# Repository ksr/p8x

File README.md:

# P8X — Hand-Built 8-Bit TTL CPU

A from-scratch 8-bit CPU built from ~130 74HCT logic chips on an 8-slot DIN41612 backplane. Fully microcoded; the microcode ROM images burned to the EPROMs are the same images the emulator interprets.

The machine now exists **twice**: as the TTL card set, and as an [FPGA
implementation](fpga/) of the same microarchitecture that boots the same
unmodified monitor, OS and toolchain. Both run the microcode from
`microcode/genucode.py`, and the C emulator is the golden reference for both.

The FPGA build also carries a **PGC-class graphics engine** (480x272
RGB565 panel, hardware 3D transforms, command lists, a fabric-parsed
graphics language modeled on the Matrox PG-640A) — see the
[theory of operation](docs/p8x-graphics-theory.md) and the
[graphics programmer's guide](docs/p8x-graphics-guide.md).

New to the abbreviations and signal names? See [GLOSSARY.md](GLOSSARY.md).

**Who made it:** I designed P8X, and it runs on an FPGA. Claude, Anthropic's AI, has been directly involved in its design, coding and documentation. — Ken Rother

## Architecture

- **8-bit data bus, 16-bit address bus**
- **4 × 16-bit pointer registers** (74169 up/down counters): P0 = PC, P1/P2 = general-purpose, P3 = stack pointer (empty-descending). The address bus is *always* driven by one of these — no separate MAR.
- **Registers:** A, B (ALU operands), T/T2 (hidden microcode temporaries), FLAGS (C, Z, N, V)
- **ALU:** 2 × 74181 + 74182 carry-lookahead, with a post-ALU shifter
- **Microcoded control:** 4 × 28C64 EEPROMs; ROM address = IR | step<<8 | cond<<12; **143 opcodes** defined in `microcode/genucode.py` (256 encodings available)
- **Memory map (rev E):** `$0000–$17FF` ROM (6 KB; shrunk from 8 KB 2026-09-14), `$1800–$FEFF` RAM (2× 62256; $1800–$1FFF is a scratch island), `$FF00–$FFFF` I/O (every data address is single-sourced in [`generators/gen_memmap.py`](generators/gen_memmap.py) → `memmap.inc`/`.h`/`.py`; commands pull the scratch/graphics/TPA-base symbols via `//#use mem`)

## Cards

The TTL machine is six core cards plus a PS/2 input card on the backplane, and a
bus test card for bring-up. Every board is designed and routed in **KiCad** (4-layer;
the plug-in cards are 280 × 140 mm) with orderable Gerbers in `hardware/<board>/kicad/`;
none has been fabricated yet. See [hardware/KICAD-BOARDS.md](hardware/KICAD-BOARDS.md)
and [hardware/RECONCILIATION.md](hardware/RECONCILIATION.md) (build readiness).

| Card | Function |
|------|----------|
| Control / Microcode | Clock, reset, sequencer, microcode EPROMs, IR, condition mux, front-panel |
| Register Bank | P0–P3 16-bit pointer registers, address bus drivers |
| ALU | A, B, T, T2 registers; 74181 ALU; shifter; FLAGS |
| Memory | 28C256 EEPROM (6 KB ROM window) + 2× 62256 SRAM, address decode (rev F) |
| I/O | Switches, LEDs, bus monitor, two 6850 ACIAs (RS-232, two DB9s) |
| CF-IDE | Two CompactFlash drives in 8-bit True IDE mode, at $FF10–$FF17 and $FF18–$FF1F |
| PS/2 | Keyboard + mouse ports at $FF58–$FF5F; an ATmega1284P behind a latch bridge |
| Bus test | Bring-up tool: a Raspberry Pi Pico drives the bus one microcycle at a time over USB |

The cards plug into a passive 8-slot backplane over a 96-pin DIN 41612 bus (rev C2).
The Eagle CAD of the first board generation is frozen (rev E) in each board's
`eagle-deprecated/` directory.

## Toolchain

| Tool | Location | Purpose |
|------|----------|---------|
| `microcode/genucode.py` | `microcode/` | Microcode generator → `u0–u3.bin` EPROM images |
| `assembler/p8xasm.py` | `assembler/` | Two-pass assembler, shares opcode table with genucode.py |
| `emulator/p8xemu.c` | `emulator/` | Cycle-accurate emulator, interprets the same u0–u3.bin images |
| `firmware/p8xmon.asm` | `firmware/` | ROM monitor (E/D/I/F/B/G/? commands) + BIOS jump table at `$0100` |
| `os/p8xos.asm` | `os/` | P8X/OS, RAM-resident disk OS booted from CF ([guide](os/README.md)) |
| `tools/p8xfs.py` | `tools/` | Host-side P8XFS disk-image tool (create/boot/put/get/ls) |
| `basic/p8xbasic.asm` | `basic/` | BASIC interpreter — disk-bootable or run-from-OS builds ([guide](basic/README.md)) |
| `apps/p8xedit.asm`, `apps/p8xasm.asm`, `apps/p8xcc.asm` | `apps/` | On-target toolchain: line editor + native two-pass assembler + native C compiler (`cc`), as `/bin` programs ([guide](apps/README.md)) |
| `compiler/p8cc.py` | `compiler/` | C cross-compiler (subset) → P8X asm → RUNnable `.bin` ([guide](compiler/README.md)) |
| `generators/gen_p8xopc.py` | `generators/` | Opcode table for the native assembler, generated from `genucode.OPC` |
| `generators/gen_eagle.py` | `generators/` | The canonical board netlists (`CARDS`, `busnet()`); its Eagle output is frozen at rev E |
| `generators/gen_kicad.py`, `build.sh` | `generators/` | KiCad boards from those netlists: placement, Freerouting, Gerbers, and the ERC/DRC readiness check |

**Generators are canon.** Never hand-edit board files (`.kicad_pcb`, and the frozen Eagle `.sch`/`.brd`) or ROM binaries — they are build artifacts. Edit the generator and regenerate. See [generators/README.md](generators/README.md) for what each script does and how to run it.

## Quick Start

Setting up a new machine? See [SETUP.md](SETUP.md) for the full toolchain, tier by
tier, and run `python3 tools/setup_check.py` to see what is installed and what each
work area still needs. Only the core-software tier is required to build and test.

```sh
# Build the emulator and regenerate microcode images
cd emulator && make

# Run the smoke tests (message print, JSR/RTS round-trip, branch countdown)
make test

# Rebuild a KiCad board: placement -> Freerouting -> Gerbers + renders -> the
# ERC/gate-sim/DRC/keepout/fab readiness check (needs KiCad 10 and a Freerouting
# jar; `all` builds every board). The netlists come from generators/gen_eagle.py.
cd ..
sh generators/build.sh memory-card
sh generators/check_card.sh memory-card          # the readiness check alone

# Reference PDFs (run from anywhere):
cd hardware
python3 ../generators/gen_bus_pdf.py              # bus definition PDF (hardware/backplane/)
python3 ../microcode/gen_progguide.py             # programmer's guide (-> docs/)
```

### EEPROM / programmer images

Both build paths emit **Intel HEX** alongside the raw `.bin`, for loading into an
EEPROM programmer:

- **Microcode** — `microcode/genucode.py` writes `u0–u3.bin` (what the emulator
  and tests load); the matching Intel HEX for the four 28C64 control-store EPROMs
  is produced into `rom/` by `make rom` (see below).
- **Program ROM** — the assembled monitor + BIOS for the 28C256 at `$0000`
  (about 4.9 KB of the 6 KB window; BASIC is no longer ROM-resident). `make rom` builds it into `rom/`.
- **Any other binary** — `python3 tools/bin2hex.py in.bin out.hex [base]`
  (e.g. a monitor built directly with `p8xasm.py`).

For a ready-to-burn set at fixed paths, run `cd emulator && make rom` (or
`sh tools/build_rom.sh`). It refreshes the four control-store EPROMs in
`microcode/` and writes the program ROM to `rom/p8x-prog-rom.{bin,hex}`. Both
are committed; see [rom/README.md](rom/README.md) for the chip map.

## Documentation

The documents below are also built into the project website, [p8x.cottageworker.com](https://p8x.cottageworker.com) (`website/`, MkDocs; published on every push to `main`).

| Document | Description |
|----------|-------------|
| [hardware/backplane/p8x-bus-definition.md](hardware/backplane/p8x-bus-definition.md) | Authoritative 96-pin bus pinout, signal descriptions, DOE/DLD encoding, microcode word layout |
| [hardware/backplane/p8x-backplane-design.md](hardware/backplane/p8x-backplane-design.md) | PCB stackup, termination analysis, BOM |
| [docs/p8x-card-standards.md](docs/p8x-card-standards.md) | Design rules that apply to every plug-in card |
| [docs/p8x-system-design.md](docs/p8x-system-design.md) | System and card-by-card architecture reference |
| [hardware/cf-card/p8x-cf-os-design.md](hardware/cf-card/p8x-cf-os-design.md) | CF-IDE hardware + P8X/OS design |
| [hardware/cf-card/p8xfs-v2-hierarchical.md](hardware/cf-card/p8xfs-v2-hierarchical.md) | P8XFS v2 hierarchical filesystem spec |
| [docs/p8x-programmers-guide.pdf](docs/p8x-programmers-guide.pdf) | Generated instruction set reference |
| [basic/p8x-basic-guide.md](basic/p8x-basic-guide.md) | P8X BASIC language reference (statements, expressions, graphics, examples) |
| [fpga/README.md](fpga/README.md) | FPGA build: milestones, getting started, both paths |
| [fpga/docs/architecture.md](fpga/docs/architecture.md) | FPGA module hierarchy, peripheral map, graphics, co-sim spec |
| [fpga/rtl/README.md](fpga/rtl/README.md) | What is shared vs sim-only, and the `cen` / `sc_en` contracts |
| [fpga/sim/README.md](fpga/sim/README.md) | How the co-sim trace-diff works, and the graphics frame diff |
| [BACKLOG.md](BACKLOG.md) | Live work only: NEXT / IDEAS / VERIFY / WONT-DO |
| [BACKLOG-DONE.md](BACKLOG-DONE.md) | Completed work + the project log |

### Per-card guides

Each board has its own directory under `hardware/` holding everything about it —
the KiCad board and its Gerbers, placement PDF and renders (`kicad/`), a README
explaining how the circuit works chip by chip, any board-specific design docs, and
the frozen Eagle files (`eagle-deprecated/`):

| Card | Directory |
|------|-----------|
| Control / Microcode | [hardware/control-card/](hardware/control-card/README.md) |
| Register Bank | [hardware/regbank-card/](hardware/regbank-card/README.md) |
| ALU | [hardware/alu-card/](hardware/alu-card/README.md) |
| Memory | [hardware/memory-card/](hardware/memory-card/README.md) |
| I/O | [hardware/io-card/](hardware/io-card/README.md) |
| CF-IDE | [hardware/cf-card/](hardware/cf-card/README.md) |
| PS/2 | [hardware/ps2-card/](hardware/ps2-card/README.md) |
| Bus test | [hardware/bustest-card/](hardware/bustest-card/p8x-bustest-card-design.md) |
| Backplane | [hardware/backplane/](hardware/backplane/p8x-backplane-design.md) |

## FPGA implementation

A standalone [FPGA build](fpga/) on a **Sipeed Tang Nano 20K** (Gowin GW2AR-18)
runs the whole machine — CPU, memory, ACIA console, microSD disk, and a 4.3"
480x272 graphics panel — from one chip and a USB cable. It is a **parallel track to the TTL build, not a replacement**:
same horizontal microcode word, same sequencer, same pointer/address model, so
the monitor, OS, BASIC, C compiler and assembler run **unmodified**.

| Milestone | State |
|-----------|-------|
| 0 First light (UART echo + heartbeat) | done |
| 1 CPU core in simulation, all 88 opcodes of the time | done |
| 2 ACIA + driven console in simulation | done |
| 3 Core on real hardware, full 64K map | done |
| 4 microSD disk — P8X/OS boots from card | done |
| 5 Clock-up + IRQ | next |
| 6 Graphics: 480x272 panel + drawing engine | done |

As built: **9 MHz** effective (27 MHz fabric, three phases per microcycle). The
CPU-only build is 40/46 block RAMs at ~48 MHz Fmax; adding the graphics panel takes
it to 44/46 and 13288/20736 LUT4, with Fmax measured at 38.8 MHz — still four times
the clock it runs at. P8X is programmed into the board's flash, so it comes up
standalone on power.

**Graphics** (`build.sh lcd`) adds the panel's native 480×272 framebuffer in
**RGB565 direct colour** — a pixel IS its colour, 65,536 of them — living in
the Tang Nano's in-package SDRAM behind a streaming controller, with a drawing
engine driven by BASIC in one window-space coordinate system (y up, the
PGC's own): `COLOR r,g,b` (or one packed value), `CLS`, `PIXELW`, `LINE`,
`BOX`, `CIRCLE` (a second radius gives an ellipse), `IMAGE` (draws a
P8I picture file — `tools/p8img.py` converts anything into one), the
`PIXELR(x,y)` and `RGB(r,g,b)` functions — plus the full PGC graphics
language as native statements (`MOVE`/`DRAW`/`POLY`/`RECT`, matrices, 3D,
command lists; see `man basic`). Text is the PGC's own stroke `TEXT`,
drawn card-side from the font the OS streams from `/FONT.GL` at boot
(GTEXT and its software rasterizer retired 2026-09-01). The drawing
statements emit that language; the engine lives in the device, so a
filled box costs the same handful of instructions as an empty one.
There is one geometry and no modes or palette to manage.
The same device is modelled in `p8xemu`, and the two are byte-compared frame
by frame.

**3D** (stages 7–10, `fpga/tang-nano-20k/sdram/STAGE*.md`): a wireframe
pipeline available from C in software (`//#use gfx` + `//#use g3d`),
accelerated by the **MDU** (a memory-mapped hardware multiply-divide unit at
`$FF30`), or fully on the card through the **GL engine** (`$FF50`): card-side
modeling and viewing matrices, clipping and projection, command lists stored in
SDRAM, and page-flipped double buffering. (The stage-8 geometry engine's
`$FF40` register window was retired at stage 10b; the GL engine is its
successor.) The same program picks the fastest fitted path at runtime; `cube`
on the shipped disk is a self-spinning GL command list, with the software path
as its fallback (`man cube`, `man g3d`).

**Verification is the point.** Every milestone is "make the RTL match the
emulator": the same program runs on both and their per-cycle architectural state
is diffed, so a divergence is a bug with an exact microcycle and signal rather
than a mystery. `fpga/sim/isa_test.asm` drives the original 88 opcodes through that diff;
the 55 added since are microcode only (no new hardware), and the RTL runs them from
the same images.

```sh
fpga/sim/run.sh 60000 isa_test.asm          # co-sim, the original 88 opcodes
fpga/sim/console.sh "" os/run-disk.img      # interactive console on the RTL
fpga/tang-nano-20k/build.sh cpu load        # build + program the board
```

## Status

- Emulator working: 143 opcodes, ACIA on stdin/stdout, CF-IDE disk model (`-c `), interactive I/O card (switches `-s`, LED trace `-L`), verified against microcode images
- Assembler working: two-pass, full expression support, shares opcode table with microcode generator
- KiCad boards designed and routed for the six CPU cards, the PS/2 card, the bus test card and the backplane (9 boards, 0 unconnected, Gerbers in each `kicad/`); none fabricated yet. The Eagle files of the first generation are frozen in `eagle-deprecated/`. (The standalone LED test card was a CAD-workflow trial, never built — deprecated and moved to `hardware/deprecated/led-card/`; its I/O address `$FF0C` is now free.)
- ROM monitor boots in the emulator; its filesystem hooks (`I`/`F`/`B`) run end to end against a CF image (`make test-cf`)
- P8X/OS v1.0 — full shell over flat **and hierarchical (P8XFS v2)** volumes. Built-in commands: `cd`/`mkdir`/`rmdir`/`load`/`run`/`save`/`del`/`path`/`pack`/`fsck`/`format`/`mount`/`umount`/`help`/`exit`/`man`/`sh`/`make`/`bootload` (`make` builds a target from a CWD `Makefile`; `bootload file` installs a freshly-built OS image into the boot sectors so the next `exit`+`B` runs it — the on-target OS-update step, closing the self-hosting loop) (the minimal-kernel split moved the pure-viewer/memory commands to `/bin`, including `dump`/`dep` — only `pack`/`fsck` remain resident because they mutate/scan the filesystem). **Dual CompactFlash** — a second card is **mounted at `/d1`** in one unified namespace (drive 0 is the root), so ordinary paths reach it with drive-unaware commands: `cd /d1`, `cat /d1/NOTES`, `grep x /d1/SRC/*.C`, cross-mount `cp /d1/A /B`. A single mount redirect in `FRESOLVE`/`RV_START` does the routing; **`cp -r /d1/dir /dir`** recursively copies a subtree across the mount (card provisioning), creating directories via the `SYS_MKDIR` syscall. **Userland commands in `/bin`** (written in C, run by bare name via implicit RUN + a `/bin` search PATH, or explicit `run`): **`dir`/`pwd`/`tree`/`cat`/`wc`/`grep`/`cp`/`mv`/`head`/`tail`/`more`/`sort`/`uniq`/`sed`/`awk`/`find`/`diff`/`cmp`/`vi`/`touch`/`man`/`dump`/`dep`/`examine`/`disasm`** (`dir README.TXT` lists a file / `dir R*` a glob, `dir -R`, `cp -r`, a VT100 `vi` screen editor, `man <cmd>` reading `/man`, `awk '{print $2}'` field processing, `examine` = interactive memory examine/modify like the monitor's `E`, etc.) — see [os/commands/](os/commands/README.md). Path resolution + CWD-path prompt; I/O redirection (`<`/`>`) and two-stage pipes (`a | b`); line editing (backspace/DEL, Ctrl-D EOF, **up/down-arrow command history** — an 8-line RAM ring — and **Tab autocomplete** of commands/paths with common-prefix fill + a match list on the second Tab); **`pack`** compacts the directory tree and **`fsck`** checks integrity on-target; host-side `p8xfs.py` builds (`--v2`), navigates, and `fsck`s images (`make test-os`)
- BASIC builds two ways from one source: disk-bootable (`B`) and a run-from-OS TPA program (`run BASIC.bin`) — `make test-basic` (ROM-resident BASIC was removed to reclaim ROM space; the old standalone `$0000` build was retired in 2026-08 when BASIC's console I/O moved onto the BIOS, which needs the monitor resident)
- On-target toolchain: **EDIT** (line editor) + **ASM** (native two-pass assembler) + **CC** (a from-scratch C compiler written in asm) as `/bin` programs — edit → **compile (`cc x.c >x.asm`)** → assemble → run a program entirely on the machine; ASM output is byte-identical to the host assembler across the whole opcode table (`make test-os`, see [apps/](apps/README.md)). **Rebuild any command on-target** — every command's source rides along under `/src/commands/{c,asm}` (plus shared `lib_*` helpers), each dir carrying a real **`Makefile`** (`target: deps` + TAB recipe, with `all`/`clean`/`install` targets). The **`make`** built-in reads the CWD `Makefile`, resolves prerequisites depth-first (shared deps built once), and drives `cc`→`asm` (or `asm` alone): `cd /src/commands/c && make pwd` rebuilds one command, `make all` the whole dir into `bin/`, `make install` publishes them over `/bin`, `make clean` removes the build outputs — see [os/commands/](os/commands/README.md). (P8X shell scripts end in `.sh`; `make` uses proper Makefiles.)
- **Native C compiler — Milestone B achieved.** `apps/p8xcc.asm` (`/bin/cc`) is a from-scratch, single-pass C compiler written directly in assembly, small enough to compile C **entirely on the machine** (front *and* back end) where the optimizing `p8cc.c` codegen — ~82 KB, larger than the whole 64 KB address space — never could. Through v0.28 it covers: functions, direct **and mutual** recursion, pointers + pass-by-reference, `int`/`char` arrays with `[]` and decay, **structs** (`.`/`->`), globals, the full operator set (`+ - * / % << >> & ^ | && || ?:`, `++`/`--`/`+=`/`-=`, comparisons, unary `- ! * &`), hex/char/string literals with escapes, `//`+`/* */` comments, a recursive **`//#use`** preprocessor (splices `/lib/lib_*.c`) plus object-like **`//#define`** macros (e.g. `//#use abi` names the BIOS/OS addresses so a command writes `bios(FOPEN, RDBUF, 0)`), and the `putchar`/`puts`/`getchar`/`peek`/`poke`/`argstr`/`bios` builtins. It compiles real OS command source: **`pwd.c` → `cc` → `asm` → runs** correctly on-target. Known gaps are listed under "cc — KNOWN LIMITATIONS" in `BACKLOG-DONE.md` (with the Milestone A/B record).
- **Host C compiler** — `compiler/p8cc.py` (the primary build tool: every `/bin` command is compiled with it) plus `compiler/p8cc.c`, the same compiler rewritten in its own subset that **self-compiles** ("small C in small C", Milestone A). Full subset incl. `struct`/`union`, global initializers, and the operators above (`make test-c`, host-vs-self differential `c_selfhost_test`, see [compiler/](compiler/README.md)).
- BIOS **file API**: byte streams (`FOPEN`/`FGETB`, `FWOPEN`/`FPUTB`/`FCLOSE`), path resolution into subdirectories (`FRESOLVE`), name formatting (`FNORM`), and directory iteration (`FOPENDIR`/`FNEXT`) — the assembler rides on the streams and self-hosts (`make test-cf`)
- **FPGA (Tang Nano 20K):** the same microarchitecture in Verilog, verified against the emulator cycle-for-cycle across the original 88 opcodes, then run on real hardware — monitor over USB serial, full 64K map, and **P8X/OS booting from a microSD** with the whole `/bin` toolchain. The board wrote its own disk: `fpga/tang-nano-20k/tools/imgload.asm` streams a P8XFS image over the console and writes it with `CFWRITE`, so no host root or card reader is needed. See [fpga/](fpga/README.md)
- **Next:** multi-stage pipes (`a | b | c`); open-by-name as one syscall (`SYS_OPEN`); the IRQ-controller hardware card; hardware bring-up (DIN 41612 footprint check against the physical connectors, order the backplane first); FPGA milestone 5 (clock-up + IRQ). Current state in [docs/p8x-status.md](docs/p8x-status.md), the working list in [BACKLOG.md](BACKLOG.md)

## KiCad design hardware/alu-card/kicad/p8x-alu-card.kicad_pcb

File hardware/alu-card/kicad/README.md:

# alu-card -- KiCad

Generated by `generators/gen_kicad.py` from the canonical gen_eagle netlist
(`CARDS["alu-card"]`), same standard as the memory card: 4-layer (F/B signals,
In1=GND, In2=VCC planes), a bypass cap above each IC, a labelled LED/jumper bank,
part values on silk. Routed with Freerouting. GENERATORS ARE CANON -- edit
`gen_kicad.py` and re-run `generators/build_kicad_card.sh alu-card`.

| File | What |
|------|------|
| `p8x-alu-card.kicad_pcb` | the board |
| `p8x-alu-card.ses` | the Freerouting routing |
| `p8x-alu-card-gerbers.zip` | orderable gerbers |
| `p8x-alu-card-placement.pdf` | parts placement (refs+values) |
| `p8x-alu-card-render-top.png` / `-3d.png` | renders |

Exotic parts use the closest standard KiCad footprint (flagged when built).

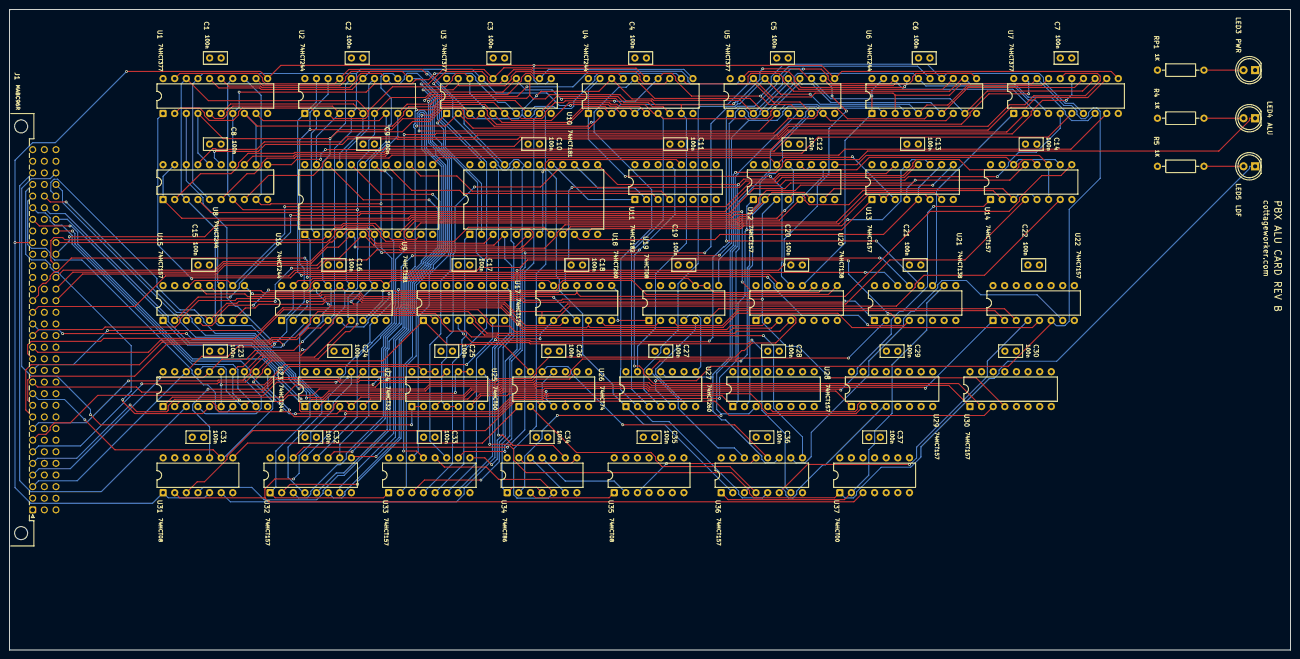
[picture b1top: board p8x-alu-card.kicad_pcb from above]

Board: 4 copper layers, 280.0 x 140.0 mm, 81 parts (0 on the bottom side), 158 nets.

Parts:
C1, C2, C3, C4, C5, C6, C7, C8, C9, C10, C11, C12, C13, C14, C15, C16, C17, C18, C19, C20, C21, C22, C23, C24, C25, C26, C27, C28, C29, C30, C31, C32, C33, C34, C35, C36, C37: 100nF; C_Disc_D5.0mm_W2.5mm_P2.50mm
J1: MABC96R; DIN41612_C_3x32_Male_Horizontal_THT
LED3, LED4: GRN; LED_D5.0mm
LED5: YEL; LED_D5.0mm
R4, R5: 1K; R_Axial_DIN0207_L6.3mm_D2.5mm_P10.16mm_Horizontal
RP1: 1K; R_Axial_DIN0207_L6.3mm_D2.5mm_P10.16mm_Horizontal
U1, U3, U5, U7: 74HCT377; DIP-20_W7.62mm
U2, U4, U6, U8, U16, U23: 74HCT244; DIP-20_W7.62mm
U9, U10: 74HCT181; DIP-24_W15.24mm
U11: 74HCT182; DIP-16_W7.62mm
U12, U13, U14, U15, U22, U28, U29, U30, U32, U33, U36: 74HCT157; DIP-16_W7.62mm
U17: 74HCT175; DIP-16_W7.62mm
U18, U27: 74HCT260; DIP-14_W7.62mm
U19, U31, U35: 74HCT08; DIP-14_W7.62mm
U20, U21: 74HCT138; DIP-16_W7.62mm
U24: 74HCT32; DIP-14_W7.62mm
U25, U37: 74HCT00; DIP-14_W7.62mm
U26: 74HCT74; DIP-14_W7.62mm
U34: 74HCT86; DIP-14_W7.62mm

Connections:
-CCLR: U26.1, U31.8
-CLRCb: U25.11, U31.10
-DOEA: U2.1, U2.19, U20.14
-DOEALU: U16.1, U16.19, U19.9, U19.10, U20.10
-DOEB: U4.1, U4.19, U20.13
-DOEFLG: U20.9, U23.1
-DOET: U6.1, U6.19, U20.12
-DOET2: U8.1, U8.19, U20.11
-LDA: U1.1, U21.14
-LDB: U3.1, U21.13
-LDFL: U21.10, U36.1, U37.2
-LDT: U5.1, U21.12
-LDT2: U7.1, U21.11
-RES: J1.a11, U17.1, U26.13, U31.9
-SETCb: U25.3, U26.4
ALUK: LED4.1, U19.8
ALUM: J1.c23, U9.8, U10.8
ALUS0: J1.c19, U9.6, U10.6
ALUS1: J1.c20, U9.5, U10.5
ALUS2: J1.c21, U9.4, U10.4, U34.9
ALUS3: J1.c22, U9.3, U10.3
AQ0: U1.2, U2.2, U9.2
AQ1: U1.5, U2.4, U9.23
AQ2: U1.6, U2.6, U9.21
AQ3: U1.9, U2.8, U9.19
AQ4: U1.12, U2.11, U10.2
AQ5: U1.15, U2.13, U10.23
AQ6: U1.16, U2.15, U10.21
AQ7: U1.19, U2.17, U10.19, U34.1, U34.4
BMX0: U9.1, U32.4
BMX1: U9.22, U32.7
BMX2: U9.20, U32.9
BMX3: U9.18, U32.12
BMX4: U10.1, U33.4
BMX5: U10.22, U33.7
BMX6: U10.20, U33.9
BMX7: U10.18, U33.12, U34.5
BQ0: U3.2, U4.2, U32.2
BQ1: U3.5, U4.4, U32.5
BQ2: U3.6, U4.6, U32.11
BQ3: U3.9, U4.8, U32.14
BQ4: U3.12, U4.11, U33.2
BQ5: U3.15, U4.13, U33.5
BQ6: U3.16, U4.15, U33.11
BQ7: U3.19, U4.17, U33.14
BSEL: J1.b28, U32.1, U33.1
CFLG: U10.16, U25.4, U25.5
CFLGI: U25.6, U29.2
CG0: U9.17, U11.3
CG1: U10.17, U11.1
CIN: J1.c24, U9.7, U11.13, U30.2
CLK: J1.a24, U1.11, U3.11, U5.11, U7.11, U31.1, U31.5
CLKFC: U26.3, U26.11, U31.3
CLKFZN: U17.9, U31.6
CLRC: J1.b27, U25.12, U25.13
CNX: U10.7, U11.12
CP0: U9.15, U11.4
CP1: U10.15, U11.2
D0: J1.a3, U1.3, U2.18, U3.3, U4.18, U5.3, U6.18, U7.3, U8.18, U16.18, U23.18, U27.1, U36.2
D1: J1.a4, U1.4, U2.16, U3.4, U4.16, U5.4, U6.16, U7.4, U8.16, U16.16, U23.16, U27.2, U36.5
D2: J1.a5, U1.7, U2.14, U3.7, U4.14, U5.7, U6.14, U7.7, U8.14, U16.14, U23.14, U27.11, U36.11
D3: J1.a6, U1.8, U2.12, U3.8, U4.12, U5.8, U6.12, U7.8, U8.12, U16.12, U23.12, U27.12, U36.14
D4: J1.a7, U1.13, U2.9, U3.13, U4.9, U5.13, U6.9, U7.13, U8.9, U16.9, U27.13
D5: J1.a8, U1.14, U2.7, U3.14, U4.7, U5.14, U6.7, U7.14, U8.7, U16.7, U27.3
D6: J1.a9, U1.17, U2.5, U3.17, U4.5, U5.17, U6.5, U7.17, U8.5, U16.5, U27.4
D7: J1.a10, U1.18, U2.3, U3.18, U4.3, U5.18, U6.3, U7.18, U8.3, U16.3, U22.6, U27.5
DLD0: J1.a16, U21.1
DLD1: J1.a17, U21.2
DLD2: J1.a18, U21.3
DLD3: J1.a19, U21.4
DOE0: J1.a12, U20.1
DOE1: J1.a13, U20.2
DOE2: J1.a14, U20.3
DOE3: J1.a15, U20.4
F0: U9.9, U12.2, U12.6, U28.2
F1: U9.10, U12.5, U12.10
F2: U9.11, U12.11, U12.13
F3: U9.13, U12.14, U13.3
F4: U10.9, U13.2, U13.6
F5: U10.10, U13.5, U13.10
F6: U10.11, U13.11, U13.13
F7: U10.13, U13.14, U28.3, U34.2
FC: J1.a27, U23.9
FENALL: U24.8, U31.4
FENC: U24.10, U31.2, U37.3
FENZN: U24.3, U24.9
FN: J1.a29, U23.5
FQC: U23.2, U23.11, U26.5, U30.3
FQN: U17.7, U23.6, U23.15
FQV: U23.8, U23.17, U26.9
FQZ: U17.2, U23.4, U23.13
FV: J1.a30, U23.3
FZ: J1.a28, U23.7
G0: U12.4, U14.2
G1: U12.7, U14.3, U14.5
G2: U12.9, U14.6, U14.11
G3: U12.12, U14.10, U14.14
G4: U13.4, U14.13, U15.2
G5: U13.7, U15.3, U15.5
G6: U13.9, U15.6, U15.11
G7: U13.12, U15.10, U15.14
GND: C1.2, C2.2, C3.2, C4.2, C5.2, C6.2, C7.2, C8.2, C9.2, C10.2, C11.2, C12.2, C13.2, C14.2, C15.2, C16.2, C17.2, C18.2, C19.2, C20.2, C21.2, C22.2, C23.2, C24.2, C25.2, C26.2, C27.2, C28.2, C29.2, C30.2, C31.2, C32.2, C33.2, C34.2, C35.2, C36.2, C37.2, J1.a31, J1.a32, J1.b3, J1.b5, J1.b7, J1.b9, J1.b11, J1.b13, J1.b15, J1.b17, J1.b19, J1.b21, J1.b23, J1.b25, J1.b31, J1.b32, J1.c31, J1.c32, LED3.1, U1.10, U2.10, U3.10, U4.10, U5.10, U6.10, U7.10, U8.10, U9.12, U10.12, U11.8, U12.8, U12.15, U13.8, U13.15, U14.8, U14.15, U15.8, U15.15, U16.10, U17.8, U17.12, U17.13, U18.7, U18.9, U18.10, U19.7, U19.12, U19.13, U20.5, U20.8, U21.5, U21.8, U22.8, U22.10, U22.11, U22.13, U22.14, U22.15, U23.10, U23.19, U24.7, U24.12, U24.13, U25.7, U26.7, U27.7, U27.9, U27.10, U28.5, U28.6, U28.8, U28.10, U28.11, U28.13, U28.14, U28.15, U29.5, U29.6, U29.8, U29.10, U29.11, U29.13, U29.14, U29.15, U30.5, U30.6, U30.8, U30.10, U30.11, U30.13, U30.14, U30.15, U31.7, U31.12, U31.13, U32.8, U32.15, U33.8, U33.15, U34.7, U35.4, U35.5, U35.7, U35.9, U35.10, U35.12, U35.13, U36.8, U36.15, U37.4, U37.5, U37.7, U37.9, U37.10, U37.12, U37.13
LDF: J1.a26, U24.1, U25.9, U25.10
LDFK: LED5.1, U25.8, U37.1
LDZN: J1.c28, U22.1, U24.2
LEDAL: LED4.2, R4.2
LEDLF: LED5.2, R5.2
LEDP: LED3.2, RP1.2
NC: U29.4, U36.3
NS2: U34.8, U34.13
NSRC: U22.7, U36.10
R0: U14.4, U16.2, U18.1
R1: U14.7, U16.4, U18.2
R2: U14.9, U16.6, U18.11
R3: U14.12, U16.8, U18.12
R4: U15.4, U16.11, U18.13
R5: U15.7, U16.13, U18.3
R6: U15.9, U16.15, U18.4
R7: U15.12, U16.17, U18.5, U22.5
RC: U26.2, U36.4
RN: U17.5, U36.9
RV: U26.12, U36.12
RZ: U17.4, U36.7
SETC: J1.c30, U25.1, U25.2
SH0: J1.c25, U12.1, U13.1, U24.4, U28.1
SH1: J1.c26, U14.1, U15.1, U24.5
SHANY: U24.6, U29.1
SHCIN: J1.c29, U30.1
SHIN: U12.3, U15.13, U30.4
SHOUT: U28.4, U29.3
T2Q0: U7.2, U8.2
T2Q1: U7.5, U8.4
T2Q2: U7.6, U8.6
T2Q3: U7.9, U8.8
T2Q4: U7.12, U8.11
T2Q5: U7.15, U8.13
T2Q6: U7.16, U8.15
T2Q7: U7.19, U8.17
TQ0: U5.2, U6.2, U32.3
TQ1: U5.5, U6.4, U32.6
TQ2: U5.6, U6.6, U32.10
TQ3: U5.9, U6.8, U32.13
TQ4: U5.12, U6.11, U33.3
TQ5: U5.15, U6.13, U33.6
TQ6: U5.16, U6.15, U33.10
TQ7: U5.19, U6.17, U33.13
VCC: C1.1, C2.1, C3.1, C4.1, C5.1, C6.1, C7.1, C8.1, C9.1, C10.1, C11.1, C12.1, C13.1, C14.1, C15.1, C16.1, C17.1, C18.1, C19.1, C20.1, C21.1, C22.1, C23.1, C24.1, C25.1, C26.1, C27.1, C28.1, C29.1, C30.1, C31.1, C32.1, C33.1, C34.1, C35.1, C36.1, C37.1, J1.a1, J1.a2, J1.b1, J1.b2, J1.c1, J1.c2, R4.1, R5.1, RP1.1, U1.20, U2.20, U3.20, U4.20, U5.20, U6.20, U7.20, U8.20, U9.24, U10.24, U11.5, U11.6, U11.14, U11.15, U11.16, U12.16, U13.16, U14.16, U15.16, U16.20, U17.16, U18.14, U19.14, U20.6, U20.16, U21.6, U21.16, U22.16, U23.20, U24.14, U25.14, U26.10, U26.14, U27.14, U28.16, U29.16, U30.16, U31.14, U32.16, U33.16, U34.10, U34.14, U35.14, U36.16, U37.14
VSRC: U35.3, U36.13
VX1: U34.3, U35.1
VX2: U34.6, U34.12
VX4: U34.11, U35.2
ZBH: U19.5, U27.6
ZBL: U19.4, U27.8
ZBUS: U19.6, U22.3
ZFLG: U19.3, U22.2
ZH: U18.6, U19.2
ZL: U18.8, U19.1
ZSRC: U22.4, U36.6

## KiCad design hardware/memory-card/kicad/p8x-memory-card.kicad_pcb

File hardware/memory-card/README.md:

# Memory Card

> **Theory of operation:** [p8x-memory-card-theory.md](p8x-memory-card-theory.md) — deep walkthrough of inputs/outputs, signal flow, and logic.

Provides the system's ROM and RAM and gates them onto the data bus. It decodes the
address bus to pick ROM vs RAM, keeps both off the data bus during I/O accesses,
and generates a clean write strobe.

> **Build the KiCad rev F board.** The 2026-09-14 ROM shrink made the map
> **6 KB ROM `$0000–$17FF`** with **`$1800–$1FFF` a RAM scratch island** (written
> by the OS/BIOS, so it must be RAM). The KiCad board in [`kicad/`](kicad/README.md)
> (rev F, routed, not yet fabricated) implements that decode on three spare gates,
> with no new chips: ROM `!CE` gains an `A11·A12` term and low-RAM U10 widens to
> `$1800–$7FFF`. The chip-by-chip text below describes the **rev E** netlist in
> `gen_eagle.py` (8 KB ROM, `$0000–$1FFF`), which `kicad/mem_revf.py` rewires to
> rev F for both the KiCad board and its schematic; the frozen Eagle `.sch` in `eagle-deprecated/` is rev E too and
> must not be built.

| Region | Device | Size |
|--------|--------|------|
| `$0000–$17FF` | 28C64 ROM (U1) | 6 KB — monitor + BIOS (BASIC is a disk program) |
| `$1800–$1FFF` | 62256 SRAM (U10) | 2 KB scratch island (IBUF/SBUF/BIOS scratch) |
| `$2000–$7FFF` | 62256 SRAM (U10) | 24 KB |
| `$8000–$FEFF` | 62256 SRAM (U2) | 32 KB (minus the I/O page) |
| `$FF00–$FFFF` | — (I/O page) | RAM inhibited; handled by I/O & CF cards |

(Rev E after the 2026-09-14 shrink: 6 KB ROM at `$0000–$17FF`; two 62256 cover
`$1800–$FEFF` = 58 KB; OS loads at `$2000`.)

> This README describes the circuit as actually built in
> [`generators/gen_eagle.py`](../../generators/gen_eagle.py). See
> [p8x-system-design.md §6](../../docs/p8x-system-design.md) for the overview and
> [p8x-bus-definition.md](../backplane/p8x-bus-definition.md) for bus pins.

## Chip inventory

| Ref | Device | Role |
|-----|--------|------|
| U1 | 28C256 (low 8 KB used; or a 28C64) | ROM (rev E: 8 KB, $0000–$1FFF; rev F: 6 KB, $0000–$17FF) |
| U2 | 62256 | SRAM, 32 KB (`$8000–$FEFF`) |
| U10 | 62256 | SRAM, 24 KB (`$2000–$7FFF`, rev E; `$1800–$7FFF` in rev F) |
| U3 | 74245 | Bidirectional data-bus transceiver |
| U4 | 7430 | 8-input NAND — I/O page ($FFxx) detector |
| U5 | 74138 | DOE decoder (read enable) |
| U6 | 74138 | DLD decoder (write strobe) |
| U7 | 74HCT00 | NAND — RAM chip-select logic |
| U8 | 74HCT32 | OR — write-strobe gating |
| U9 | 74HCT08 | AND — transceiver enable (rev F: spare gate U9.4 = `A11·A12`) |
| U11 | 74HCT32 | OR — ROM `!CE` (rev E: A13 OR A14 OR A15; rev F adds the `A11·A12` term on U11.2/U11.3) |

## How it works

### Address decode (ROM vs RAM vs I/O) — rev E, decoded from A13 + A14 + A15
- **ROM** (U1) is selected when **A13 = A14 = A15 = 0** — `!CE = A13 OR A14 OR A15`,
  so the ROM responds for `$0000–$1FFF` (8 KB).
- **Low RAM** (62256, U10) is selected when **A15 = 0 and (A13 or A14) = 1** —
  `!CE = A15 OR NOR(A13, A14)`, covering `$2000–$7FFF` (deselected in the
  `$0000–$1FFF` ROM page).
- The **I/O page detector** (U4, a 7430 8-input NAND on A8–A15) asserts `-IOPG` low
  whenever the address is `$FFxx`.
- **Main RAM** (62256, U2) is selected only when **A15 = 1 *and* not the I/O page**.
  U7 NANDs A15 with `-IOPG` to produce `-RAMCE`: RAM enables for `$8000–$FEFF` but
  stays off for `$FFxx`, leaving that page to the I/O and CF cards.

The rev-E decode adds the A13 term to the ROM/RAM-low select. rev D's spare gates
were used up, so rev E adds exactly one 2-input gate: **U11.1** (a 74HCT32 OR).
The rev-D gates are reused in place — `U8.4` now ORs `A13,A14` into `Q`; `U11.1`
ORs `Q` with `A15` for the ROM `!CE` (`A13|A14|A15`); and `U7.3` NANDs `!A15` with
`Q` for the RAM-low `!CE` (= `A15 OR NOR(A13,A14)`). U11's 100 nF cap is `C11`.

### Data-bus transceiver
The 74245 (U3) connects on-card memory to the backplane data bus. Its **direction**
is set by read vs write: on a read (DOE = 7 → `-RD`) it drives the bus from memory;
on a write (DLD = 7 → `-MEMW`) it drives memory from the bus. It is **enabled on a
memory read or write outside the I/O page**: `-BOE = OR(AND(-RD, -MEMW), IOPG)`,
with `AND(-RD, -MEMW)` in U9.1, `IOPG` (the I/O page, active high) from `U7.4`
wired as an inverter on `-IOPG`, and the OR in `U11.4`. In `$FF00–$FFFF` the
buffer stays off, so the card never drives D0–D7 while the I/O, CF or PS/2 card
answers. (Until 2026-11-26 the drawn rev F had `-BOE = AND(-RD, -MEMW)` alone:
every read of the I/O page turned U3 on and drove the undriven memory data lines
onto the bus against the I/O card. Found before any board was made; the gate-level
simulation `tools/gatesim/run.sh` now checks the buffer for every address.)

### Read path
DOE code 7 (`-RD`, decoded by U5) drives the memory output-enables (`!OE`) and sets
the 74245 direction toward the bus. The selected chip (ROM or RAM, per the decode
above) puts its byte on the bus.

### Write path & strobe timing
DLD code 7 (`-MEMW`, decoded by U6) is the write request. The actual `!WE` strobe is
`-MEMW` **gated with CLK̄** in U8: this gives address and data a full half-cycle to
set up before the write pulse falls in the second half-cycle — clean, glitch-free
writes. Only RAM responds to writes; the EEPROM `!WE` is held inactive (in-system
EEPROM programming is out of scope for normal operation).

## Bus codes this card owns
- **DOE:** 7 = memory read (drives D0–D7)
- **DLD:** 7 = memory write (`MEMW` strobe) — shared decode convention with the I/O card

## LEDs
PWR (green), ROM (yellow), RAM (yellow), RD (green), WR (red) — show which region
and direction is active each cycle. **RAM2 (yellow, rev E)** lights when the new
`$1800–$7FFF` bank (U10) is addressed — a bank-select indicator. Its cathode sits
on `-RAM2CE` itself (VCC – `RS5` – LED – `-RAM2CE`), so it needs no gate; it is not
`-BOE`-gated like the ROM and RAM LEDs. (Through 2026-11-25 a `U7` gate inverted
`-RAM2CE` to source it; that gate now makes `IOPG` for the buffer enable.)

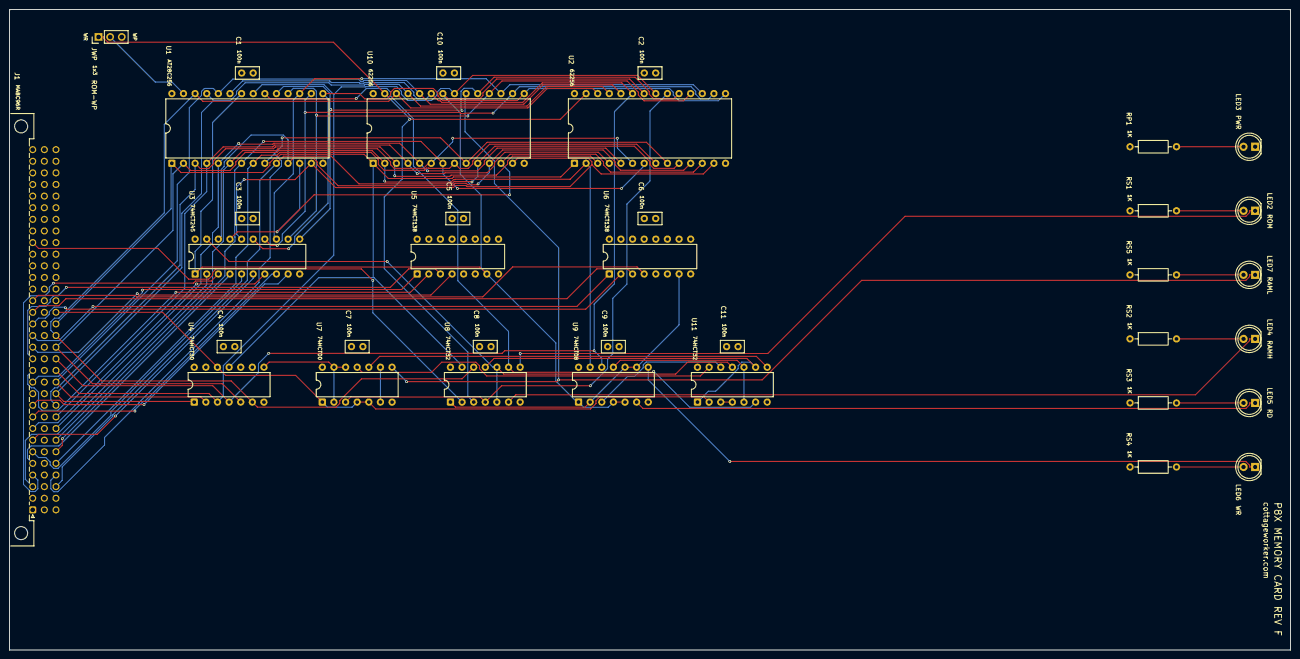
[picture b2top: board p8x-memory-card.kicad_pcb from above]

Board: 4 copper layers, 280.0 x 140.0 mm, 36 parts (0 on the bottom side), 69 nets.

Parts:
C1, C2, C3, C4, C5, C6, C7, C8, C9, C10, C11: 100nF; C_Disc_D5.0mm_W2.5mm_P2.50mm
J1: MABC96R; DIN41612_C_3x32_Male_Horizontal_THT
JWP: 1x3; PinHeader_1x03_P2.54mm_Vertical
LED2, LED4, LED7: YEL; LED_D5.0mm
LED3, LED5: GRN; LED_D5.0mm
LED6: RED; LED_D5.0mm
RP1: 1K; R_Axial_DIN0207_L6.3mm_D2.5mm_P10.16mm_Horizontal
RS1, RS2, RS3, RS4, RS5: 1K; R_Axial_DIN0207_L6.3mm_D2.5mm_P10.16mm_Horizontal
U1: 28C256; DIP-28_W15.24mm
U2, U10: 62256; DIP-28_W15.24mm
U3: 74HCT245; DIP-20_W7.62mm
U4: 74HCT30; DIP-14_W7.62mm
U5, U6: 74HCT138; DIP-16_W7.62mm
U7: 74HCT00; DIP-14_W7.62mm
U8, U11: 74HCT32; DIP-14_W7.62mm
U9: 74HCT08; DIP-14_W7.62mm

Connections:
-ACC: U9.3, U11.12
-BOE: U3.19, U8.5, U8.10, U11.11
-IOPG: U4.8, U7.2, U7.12, U7.13
-MEMW: U6.7, U8.1, U9.2, U9.9, U9.10
-RAM2CE: LED7.1, U7.8, U10.20
-RAMCE: U2.20, U7.3, U8.4
-RD: U1.22, U2.22, U3.1, U5.7, U9.1, U9.4, U9.5, U10.22
-WE: JWP.1, U2.27, U8.3, U10.27
A0: J1.c3, U1.10, U2.10, U10.10
A1: J1.c4, U1.9, U2.9, U10.9
A2: J1.c5, U1.8, U2.8, U10.8
A3: J1.c6, U1.7, U2.7, U10.7
A4: J1.c7, U1.6, U2.6, U10.6
A5: J1.c8, U1.5, U2.5, U10.5
A6: J1.c9, U1.4, U2.4, U10.4
A7: J1.c10, U1.3, U2.3, U10.3
A8: J1.c11, U1.25, U2.25, U4.1, U10.25
A9: J1.c12, U1.24, U2.24, U4.2, U10.24
A10: J1.c13, U1.21, U2.21, U4.3, U10.21
A11: J1.c14, U1.23, U2.23, U4.4, U9.12, U10.23
A12: J1.c15, U1.2, U2.2, U4.5, U9.13, U10.2
A13: J1.c16, U1.26, U2.26, U4.6, U8.12, U10.26
A14: J1.c17, U1.1, U2.1, U4.11, U8.13, U10.1
A15: J1.c18, U4.12, U7.1, U7.4, U7.5, U11.2
A15N: U7.6, U7.9
CLK: J1.a24, U8.2
D0: J1.a3, U3.2
D1: J1.a4, U3.3
D2: J1.a5, U3.4
D3: J1.a6, U3.5
D4: J1.a7, U3.6
D5: J1.a8, U3.7
D6: J1.a9, U3.8
D7: J1.a10, U3.9
DLD0: J1.a16, U6.1
DLD1: J1.a17, U6.2
DLD2: J1.a18, U6.3
DLD3: J1.a19, U6.4
DOE0: J1.a12, U5.1
DOE1: J1.a13, U5.2
DOE2: J1.a14, U5.3
DOE3: J1.a15, U5.4
GND: C1.2, C2.2, C3.2, C4.2, C5.2, C6.2, C7.2, C8.2, C9.2, C10.2, C11.2, J1.a31, J1.a32, J1.b3, J1.b5, J1.b7, J1.b9, J1.b11, J1.b13, J1.b15, J1.b17, J1.b19, J1.b21, J1.b23, J1.b25, J1.b31, J1.b32, J1.c31, J1.c32, LED3.1, U1.14, U2.14, U3.10, U4.7, U5.5, U5.8, U6.5, U6.8, U7.7, U8.7, U9.7, U10.14, U11.7
IOPG: U7.11, U11.13
LEDP: LED3.2, RP1.2
LEDRA: LED4.2, RS2.2
LEDRA2: LED7.2, RS5.2
LEDRD: LED5.2, RS3.2
LEDRO: LED2.2, RS1.2
LEDWR: LED6.2, RS4.2
MD0: U1.11, U2.11, U3.18, U10.11
MD1: U1.12, U2.12, U3.17, U10.12
MD2: U1.13, U2.13, U3.16, U10.13
MD3: U1.15, U2.15, U3.15, U10.15
MD4: U1.16, U2.16, U3.14, U10.16
MD5: U1.17, U2.17, U3.13, U10.17
MD6: U1.18, U2.18, U3.12, U10.18
MD7: U1.19, U2.19, U3.11, U10.19
P: U9.11, U11.5, U11.10
Q: U8.11, U11.1, U11.9
RAMK: LED4.1, U8.6
RDK: LED5.1, U9.6
ROMCE: U1.20, U8.9, U11.6
ROMK: LED2.1, U8.8
ROMOR3: U11.3, U11.4
ROMWE: JWP.2, U1.27
S: U7.10, U11.8
VCC: C1.1, C2.1, C3.1, C4.1, C5.1, C6.1, C7.1, C8.1, C9.1, C10.1, C11.1, J1.a1, J1.a2, J1.b1, J1.b2, J1.c1, J1.c2, JWP.3, RP1.1, RS1.1, RS2.1, RS3.1, RS4.1, RS5.1, U1.28, U2.28, U3.20, U4.14, U5.6, U5.16, U6.6, U6.16, U7.14, U8.14, U9.14, U10.28, U11.14
WRK: LED6.1, U9.8

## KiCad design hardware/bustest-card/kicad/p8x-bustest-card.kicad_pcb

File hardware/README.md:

# hardware/

The physical machine: one passive backplane, six plug-in CPU cards, a PS/2 input
card, and a bus test card for bring-up. Each board has its own directory holding a
chip-by-chip README, a theory of operation or design doc, and the **KiCad** board
(`kicad/`: the `.kicad_pcb`, the Freerouting session, orderable Gerbers, a
placement PDF and renders). Every board is designed and routed; none has been
fabricated yet. Board status: **[KICAD-BOARDS.md](KICAD-BOARDS.md)**; build
readiness against the emulator and the FPGA: **[RECONCILIATION.md](RECONCILIATION.md)**.

| Board | Directory | Function |
|-------|-----------|----------|
| Control / Microcode | [control-card/](control-card/README.md) | Clock, reset, sequencer, microcode EPROMs, IR, condition mux, front panel |
| Register Bank | [regbank-card/](regbank-card/README.md) | P0–P3 16-bit pointer registers, address-bus drivers |
| ALU | [alu-card/](alu-card/README.md) | A/B/T/T2 registers, 74181 ALU, shifter, FLAGS |
| Memory | [memory-card/](memory-card/README.md) | 28C256 ROM (6 KB window, `$0000–$17FF`) + 2× 62256 SRAM, address decode (rev F) |
| I/O | [io-card/](io-card/README.md) | Switches, LEDs, bus monitor, two 6850 ACIAs (`$FF04/05`, `$FF08/09`) with two DB9s (rev B) |
| CF-IDE | [cf-card/](cf-card/README.md) | Two CompactFlash drives in 8-bit True IDE mode: `$FF10–$FF17` and `$FF18–$FF1F` (rev B) |
| PS/2 | [ps2-card/](ps2-card/README.md) | Keyboard + mouse at `$FF58–$FF5F`: an ATmega1284P behind a latch bridge (rev A) |
| Bus test | [bustest-card/](bustest-card/p8x-bustest-card-design.md) | Bring-up tool: a Raspberry Pi Pico drives the bus over USB, one microcycle at a time |
| Backplane | [backplane/](backplane/p8x-backplane-design.md) | 8-slot passive 96-pin DIN 41612 bus (rev C2), 262 × 128 mm |

The plug-in cards are all 280 × 140 mm, 4-layer (signals on the outer layers, GND
and +5 V planes inside).

**Eagle (frozen).** The first board generation was drawn in Eagle/Fusion from
`generators/gen_eagle.py`. On 2026-09-18 the KiCad flow replaced it: each board's
Eagle `.sch`/`.brd` and its schematic and placement PDFs moved to
`<board>/eagle-deprecated/`, frozen at rev E, and are no longer maintained (the
Eagle memory card still carries the old 8 KB ROM decode; the KiCad rev F board has
the 6 KB one). `gen_eagle.py` stays the source of the netlists.

> **Deprecated:** the standalone **LED test card** (a write-only 8-LED output
> latch that decoded `$FF0C`) was a CAD-workflow trial, never built. It has been
> moved to [`deprecated/led-card/`](deprecated/led-card/) and its I/O address
> `$FF0C` is now free. (This is unrelated to the `$FF02` LED latch the emulator
> traces, which stays.) The combined I/O + CF + PS/2 **peripheral card** is parked
> in `parked/peripheral-card/` (2026-09-19); the design went back to three cards.

### Not yet realised as TTL boards
See **[RECONCILIATION.md](RECONCILIATION.md)** for the full board-vs-emulator/FPGA
build-readiness pass. Subsystems the emulator and/or the FPGA already provide that
have **no TTL card** yet:

| Subsystem | Where it lives now | TTL board |
|-----------|--------------------|-----------|
| MDU multiply/divide (`$FF30–$FF3F`) | emulator model + FPGA (`mdu_core.v`) | none yet |
| Graphics-language port (`$FF50–$FF54`) | emulator model + the Tang Nano 20K graphics card | none (the FPGA card *is* the graphics engine) |
| IRQ controller (`$FF06` device-IRQ model) | emulator model | none yet — the next card to design |

**[assembly/](assembly/README.md)** — 3D renders of the assembled machine: the
backplane with all eight cards standing in their slots, each card populated
(rendered from the boards by `generators/render_assembly.py`; slot order inside).

`p8x-bom.csv` — the orderable bill of materials for the whole machine
(ICs, sockets, connectors, passives), generated by
[`../generators/gen_bom.py`](../generators/).

## Rebuilding boards

**Generators are canon** — never hand-edit a `.kicad_pcb`. The netlists live in
[`../generators/gen_eagle.py`](../generators/) (`CARDS`, `busnet()`);
`gen_kicad.py` turns a card into a placed KiCad board (the memory, I/O, CF, PS/2
cards and the backplane have bespoke placement scripts in their `kicad/`
directories), Freerouting routes it, and `check_card.sh` runs the readiness check
(ERC, gate-level simulation where a testbench exists, DRC, mounting-hole keepout,
fab minimums). One command does all of it, from the repository root:

```sh
sh generators/build.sh memory-card      # one board (or: all)
sh generators/check_card.sh memory-card # the readiness check alone
```

It needs KiCad 10 and a Freerouting jar. See
[../generators/README.md](../generators/README.md) for the scripts and
[../docs/p8x-card-standards.md](../docs/p8x-card-standards.md) for the rules
every card follows.

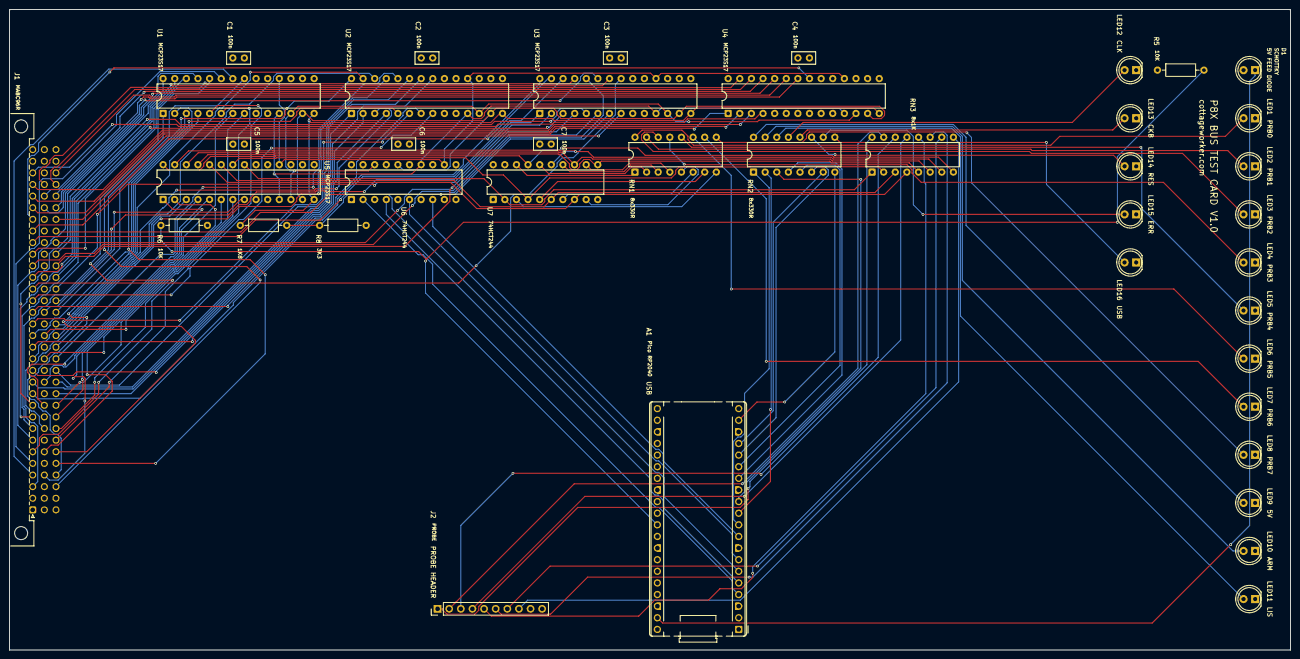
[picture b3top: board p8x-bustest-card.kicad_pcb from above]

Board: 4 copper layers, 280.0 x 140.0 mm, 41 parts (0 on the bottom side), 129 nets.

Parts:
A1: RP2040; RaspberryPi_Pico_Common_THT
C1, C2, C3, C4, C5, C6, C7: 100nF; C_Disc_D5.0mm_W2.5mm_P2.50mm
D1: SCHOTTKY; LED_D5.0mm
J1: MABC96R; DIN41612_C_3x32_Male_Horizontal_THT
J2: PROBE; PinHeader_1x10_P2.54mm_Vertical
LED1: PRB0; LED_D5.0mm
LED2: PRB1; LED_D5.0mm
LED3: PRB2; LED_D5.0mm
LED4: PRB3; LED_D5.0mm
LED5: PRB4; LED_D5.0mm
LED6: PRB5; LED_D5.0mm
LED7: PRB6; LED_D5.0mm
LED8: PRB7; LED_D5.0mm
LED9: 5V; LED_D5.0mm
LED10: ARM; LED_D5.0mm
LED11: LIS; LED_D5.0mm
LED12: CLK; LED_D5.0mm
LED13: CKB; LED_D5.0mm
LED14: RES; LED_D5.0mm
LED15: ERR; LED_D5.0mm
LED16: USB; LED_D5.0mm
R5, R6: 10K; R_Axial_DIN0207_L6.3mm_D2.5mm_P10.16mm_Horizontal
R7: 1K8; R_Axial_DIN0207_L6.3mm_D2.5mm_P10.16mm_Horizontal
R8: 3K3; R_Axial_DIN0207_L6.3mm_D2.5mm_P10.16mm_Horizontal
RN1, RN2: 8x330R; DIP-16_W7.62mm
RN3: 8x1K; DIP-16_W7.62mm
U1, U2, U3, U4, U5: MCP23S17; DIP-28_W7.62mm
U6, U7: 74HCT244; DIP-20_W7.62mm

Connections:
-RES: J1.a11, U3.28
A0: J1.c3, U1.1
A1: J1.c4, U1.2
A2: J1.c5, U1.3
A3: J1.c6, U1.4
A4: J1.c7, U1.5
A5: J1.c8, U1.6
A6: J1.c9, U1.7
A7: J1.c10, U1.8
A8: J1.c11, U2.21
A9: J1.c12, U2.22
A10: J1.c13, U2.23
A11: J1.c14, U2.24
A12: J1.c15, U2.25
A13: J1.c16, U2.26
A14: J1.c17, U2.27
A15: J1.c18, U2.28
ALUM: J1.c23, U3.5
ALUS0: J1.c19, U3.1
ALUS1: J1.c20, U3.2
ALUS2: J1.c21, U3.3
ALUS3: J1.c22, U3.4
BSEL: J1.b28, U4.25
CIN: J1.c24, U3.6
CLK: J1.a24, U3.26
CLKB: J1.a25, U3.27
CLRC: J1.b27, U4.24
CS5: U1.11, U2.11, U3.11, U4.11, U5.11, U6.14
D0: J1.a3, U1.21
D1: J1.a4, U1.22
D2: J1.a5, U1.23
D3: J1.a6, U1.24
D4: J1.a7, U1.25
D5: J1.a8, U1.26
D6: J1.a9, U1.27
D7: J1.a10, U1.28
DLD0: J1.a16, U2.5
DLD1: J1.a17, U2.6
DLD2: J1.a18, U2.7
DLD3: J1.a19, U2.8
DOE0: J1.a12, U2.1
DOE1: J1.a13, U2.2
DOE2: J1.a14, U2.3
DOE3: J1.a15, U2.4
FC: J1.a27, U4.1
FN: J1.a29, U4.3
FV: J1.a30, U4.4
FZ: J1.a28, U4.2
GND: A1.3, A1.8, A1.13, A1.18, A1.23, A1.28, A1.33, A1.38, C1.2, C2.2, C3.2, C4.2, C5.2, C6.2, C7.2, J1.a31, J1.a32, J1.b3, J1.b5, J1.b7, J1.b9, J1.b11, J1.b13, J1.b15, J1.b17, J1.b19, J1.b21, J1.b23, J1.b25, J1.b31, J1.b32, J1.c31, J1.c32, J2.9, J2.10, LED1.1, LED2.1, LED3.1, LED4.1, LED5.1, LED6.1, LED7.1, LED8.1, LED9.1, LED10.1, LED11.1, LED12.1, LED13.1, LED14.1, LED15.1, LED16.1, R6.2, R8.2, U1.10, U1.15, U1.16, U1.17, U1.19, U1.20, U2.10, U2.16, U2.17, U2.19, U2.20, U3.10, U3.15, U3.17, U3.19, U3.20, U4.10, U4.17, U4.19, U4.20, U5.10, U5.15, U5.16, U5.19, U5.20, U6.1, U6.10, U6.11, U6.13, U6.15, U6.17, U6.19, U7.1, U7.10, U7.19
IRQ: J1.b29, U4.27
LDF: J1.a26, U4.21
LDZN: J1.c28, U4.22
LK_PR0: LED1.2, RN1.16
LK_PR1: LED2.2, RN1.15
LK_PR2: LED3.2, RN1.14
LK_PR3: LED4.2, RN1.13
LK_PR4: LED5.2, RN1.12
LK_PR5: LED6.2, RN1.11
LK_PR6: LED7.2, RN1.10
LK_PR7: LED8.2, RN1.9
L_PR0: RN1.1, U7.18
L_PR1: RN1.2, U7.16
L_PR2: RN1.3, U7.14
L_PR3: RN1.4, U7.12
L_PR4: RN1.5, U7.9
L_PR5: RN1.6, U7.7
L_PR6: RN1.7, U7.5
L_PR7: RN1.8, U7.3
P5V: A1.39, D1.1
PDEC: J1.a23, U3.25
PINC: J1.a22, U3.24
PR0: RN3.1, U5.21, U7.2
PR1: RN3.2, U5.22, U7.4
PR2: RN3.3, U5.23, U7.6
PR3: RN3.4, U5.24, U7.8
PR4: RN3.5, U5.25, U7.11
PR5: RN3.6, U5.26, U7.13
PR6: RN3.7, U5.27, U7.15
PR7: RN3.8, U5.28, U7.17
PRJ0: J2.1, RN3.16
PRJ1: J2.2, RN3.15
PRJ2: J2.3, RN3.14
PRJ3: J2.4, RN3.13
PRJ4: J2.5, RN3.12
PRJ5: J2.6, RN3.11
PRJ6: J2.7, RN3.10
PRJ7: J2.8, RN3.9
PSEL0: J1.a20, U3.21
PSEL1: J1.a21, U3.22
PSEL2: J1.c27, U3.23
P_CS: A1.7, U6.6
P_MISO: A1.6, R7.2, R8.1
P_RST: A1.9, U6.8
P_SCK: A1.4, U6.2
P_SI: A1.5, U6.4
RST5: U1.18, U2.18, U3.18, U4.18, U5.18, U6.12
SCK5: U1.12, U2.12, U3.12, U4.12, U5.12, U6.18
SENSE5: A1.31, R5.2, R6.1
SETC: J1.c30, U4.23
SH0: J1.c25, U3.7
SH1: J1.c26, U3.8
SHCIN: J1.c29, U4.26
SI5: U1.13, U2.13, U3.13, U4.13, U5.13, U6.16
SO5: R7.1, U1.14, U2.14, U3.14, U4.14, U5.14
SPARE12: J1.b4, U5.1
SPARE13: J1.b6, U5.2
SPARE14: J1.b8, U5.3
SPARE15: J1.b10, U5.4
SPARE16: J1.b12, U5.5
SPARE17: J1.b14, U5.6
SPARE18: J1.b16, U5.7
SPARE19: J1.b18, U5.8
ST0: A1.10, RN2.1
ST1: A1.11, RN2.2
ST2: A1.12, RN2.3
ST3: A1.14, RN2.4
ST4: A1.15, RN2.5
ST5: A1.16, RN2.6
ST6: A1.17, RN2.7
ST7: A1.19, RN2.8
STK0: LED9.2, RN2.16
STK1: LED10.2, RN2.15
STK2: LED11.2, RN2.14
STK3: LED12.2, RN2.13
STK4: LED13.2, RN2.12
STK5: LED14.2, RN2.11
STK6: LED15.2, RN2.10
STK7: LED16.2, RN2.9
VCC: C1.1, C2.1, C3.1, C4.1, C5.1, C6.1, C7.1, D1.2, J1.a1, J1.a2, J1.b1, J1.b2, J1.c1, J1.c2, R5.1, U1.9, U2.9, U2.15, U3.9, U3.16, U4.9, U4.15, U4.16, U5.9, U5.17, U6.20, U7.20
